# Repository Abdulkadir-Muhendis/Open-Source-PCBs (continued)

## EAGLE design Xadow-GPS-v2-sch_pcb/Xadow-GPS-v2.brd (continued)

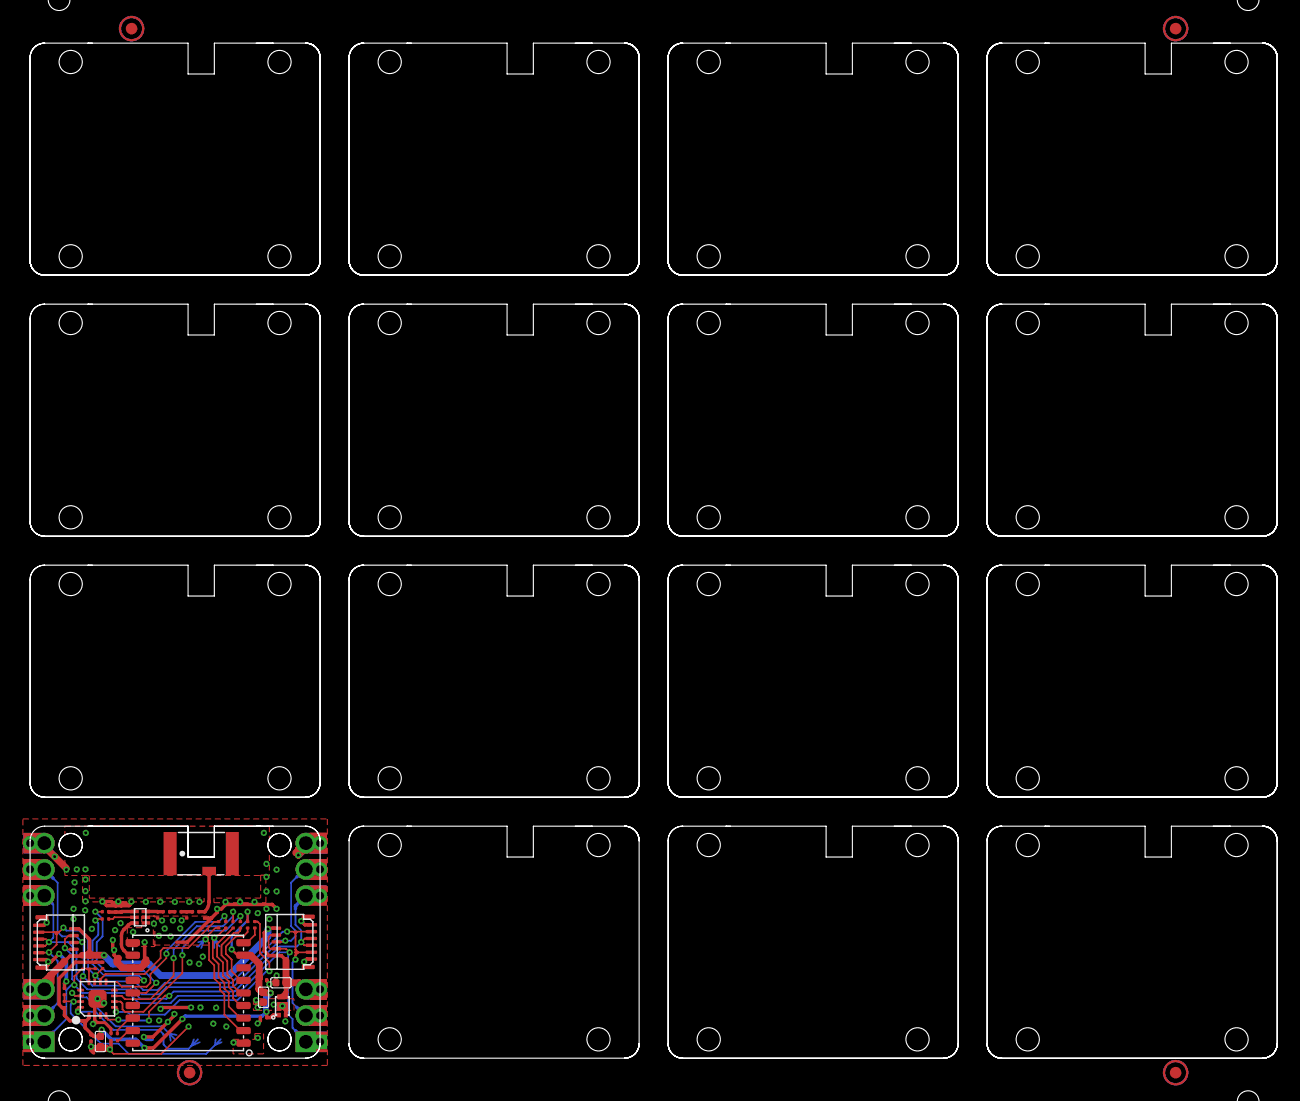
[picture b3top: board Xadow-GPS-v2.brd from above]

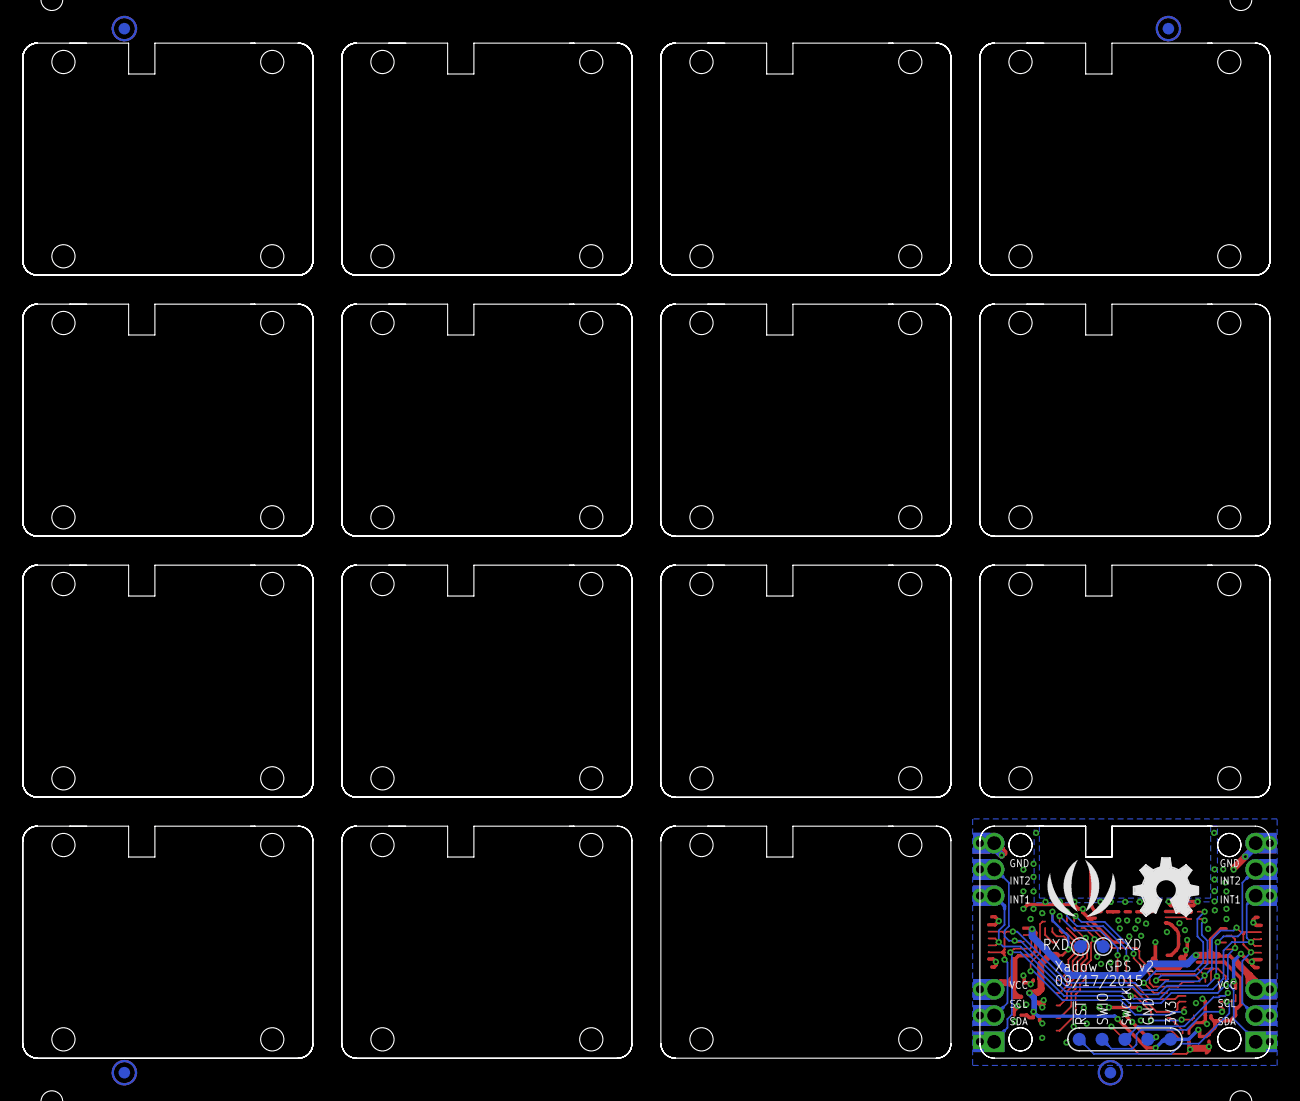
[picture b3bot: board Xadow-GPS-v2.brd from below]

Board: 2 copper layers, 109.2 x 88.9 mm, 53 parts (9 on the bottom side), 32 nets.

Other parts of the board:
U$19: OSHW_FILLX200_NOTEXT
U$21: SEEED-SILK-280*268MIL

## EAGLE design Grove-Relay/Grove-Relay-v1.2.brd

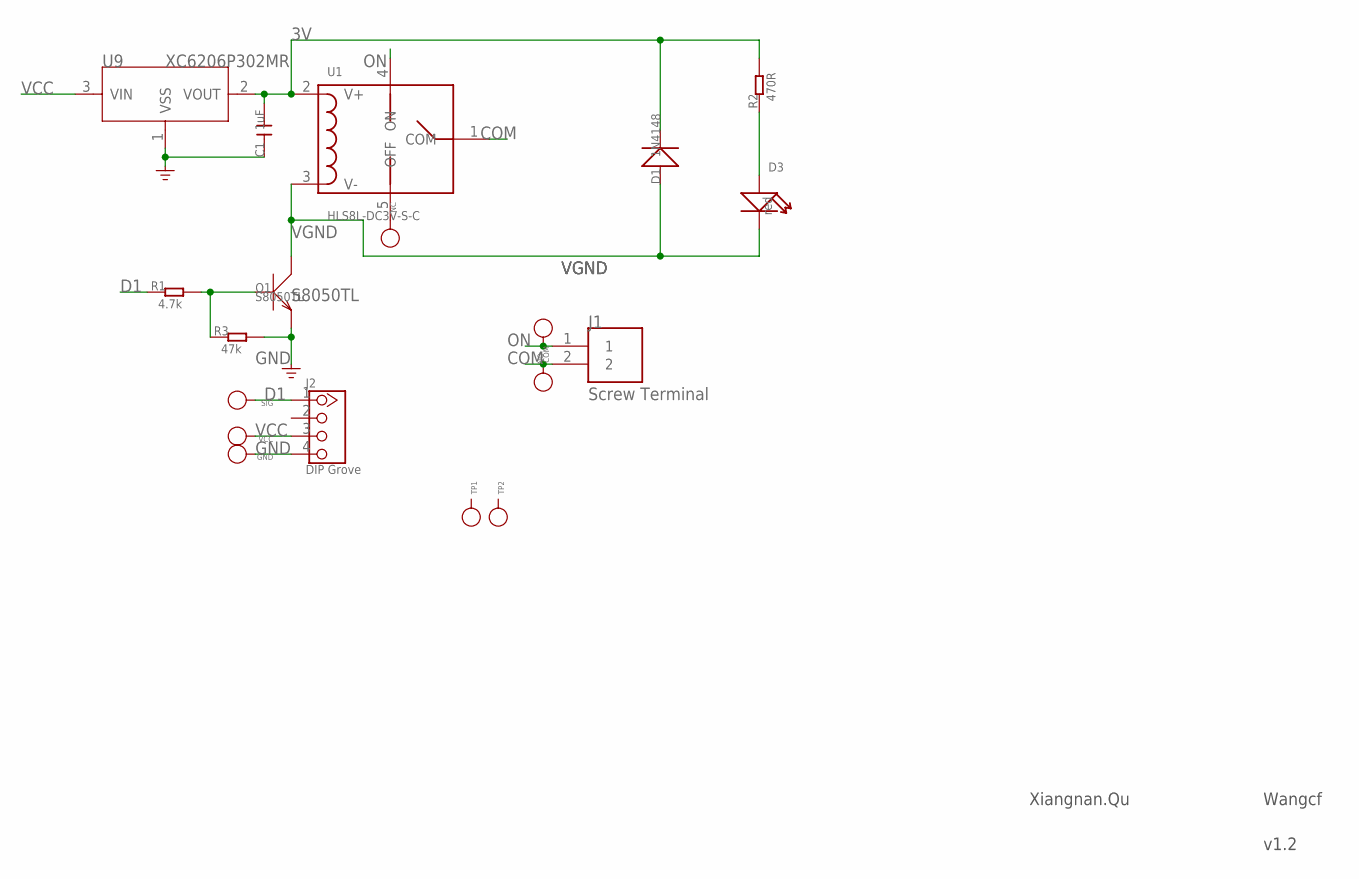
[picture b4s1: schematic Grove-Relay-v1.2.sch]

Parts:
C1: 1uF; C0603
COM: PAD-TEST-POINT'4545'; TP_4545
D1: 1N4148; LL-34
D3: red; LED-0603
GND: PAD-TEST-POINT'4545'; TP_4545
J1: Screw Terminal; CON2
J2: DIP Grove; 2.0_1X4
NC: PAD-TEST-POINT'4545'; TP_4545
NO: PAD-TEST-POINT'4545'; TP_4545
Q1: S8050TL; SOT23
R1: 4.7k; R0603
R2: 470R; R0603
R3: 47k; R0603
SIG: PAD-TEST-POINT'4545'; TP_4545
TP1, TP2: PAD-TEST-POINT'4545'; TP_4545
U1: HLS8L-DC3V-S-C; RELAY
U9: XC6206P302MR; SOT23
VCC: PAD-TEST-POINT'4545'; TP_4545

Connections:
3V: C1.2, D1.C (-), R2.2, U1.2 (V+), U9.2 (VOUT)
COM: COM.T, J1.2, U1.1 (COM)
D1: J2.1, R1.1, SIG.T
GND: C1.1, GND.T, J2.4, Q1.2 (E), R3.2, U9.1 (VSS)
unnamed: D3.+, R2.1
unnamed: Q1.1 (B), R1.2, R3.1
unnamed: NC.T, U1.5 (OFF)
ON: J1.1, NO.T, U1.4 (ON)
VCC: J2.3, U9.3 (VIN), VCC.T
VGND: D1.A (+), D3.-, Q1.3 (C), U1.3 (V-)

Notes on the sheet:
S8050TL
Xiangnan.Qu
Wangcf
v1.2

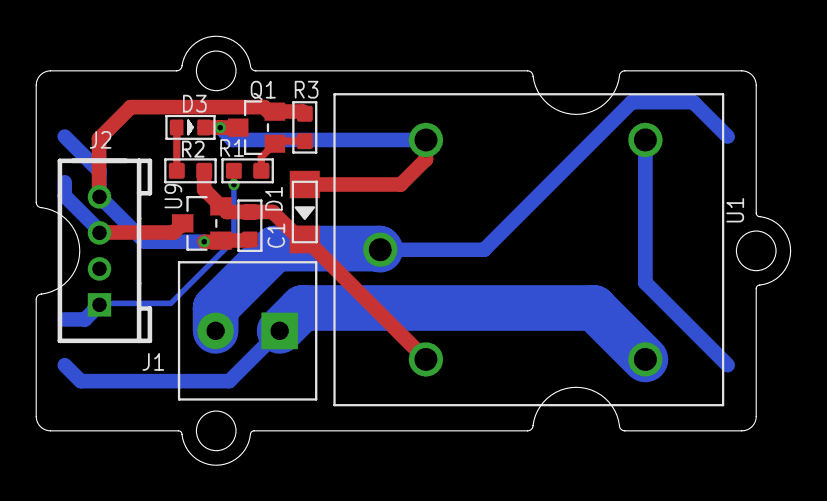
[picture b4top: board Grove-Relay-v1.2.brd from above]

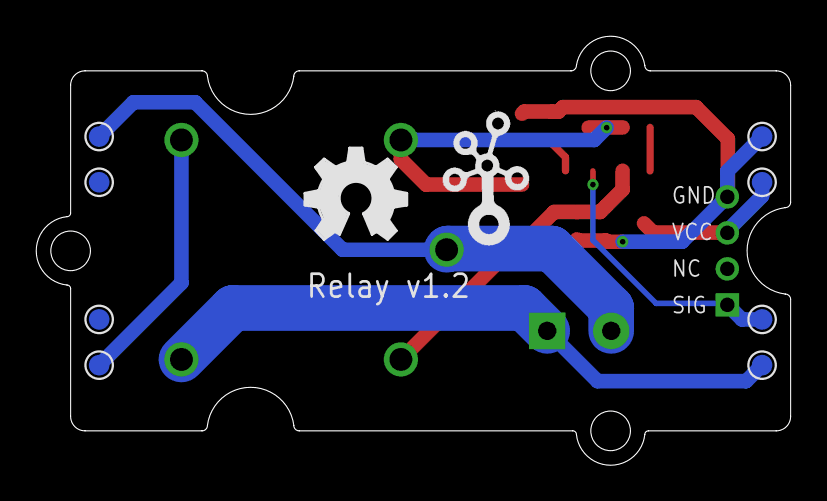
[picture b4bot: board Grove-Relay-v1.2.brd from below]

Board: 2 copper layers, 41.9 x 23.8 mm, 22 parts (10 on the bottom side), 10 nets.

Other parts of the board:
U$2: OSHW_FILLX200_NOTEXT
U$3: GROVE-TEST-PLATFORM
U$5: TWIGLOGO

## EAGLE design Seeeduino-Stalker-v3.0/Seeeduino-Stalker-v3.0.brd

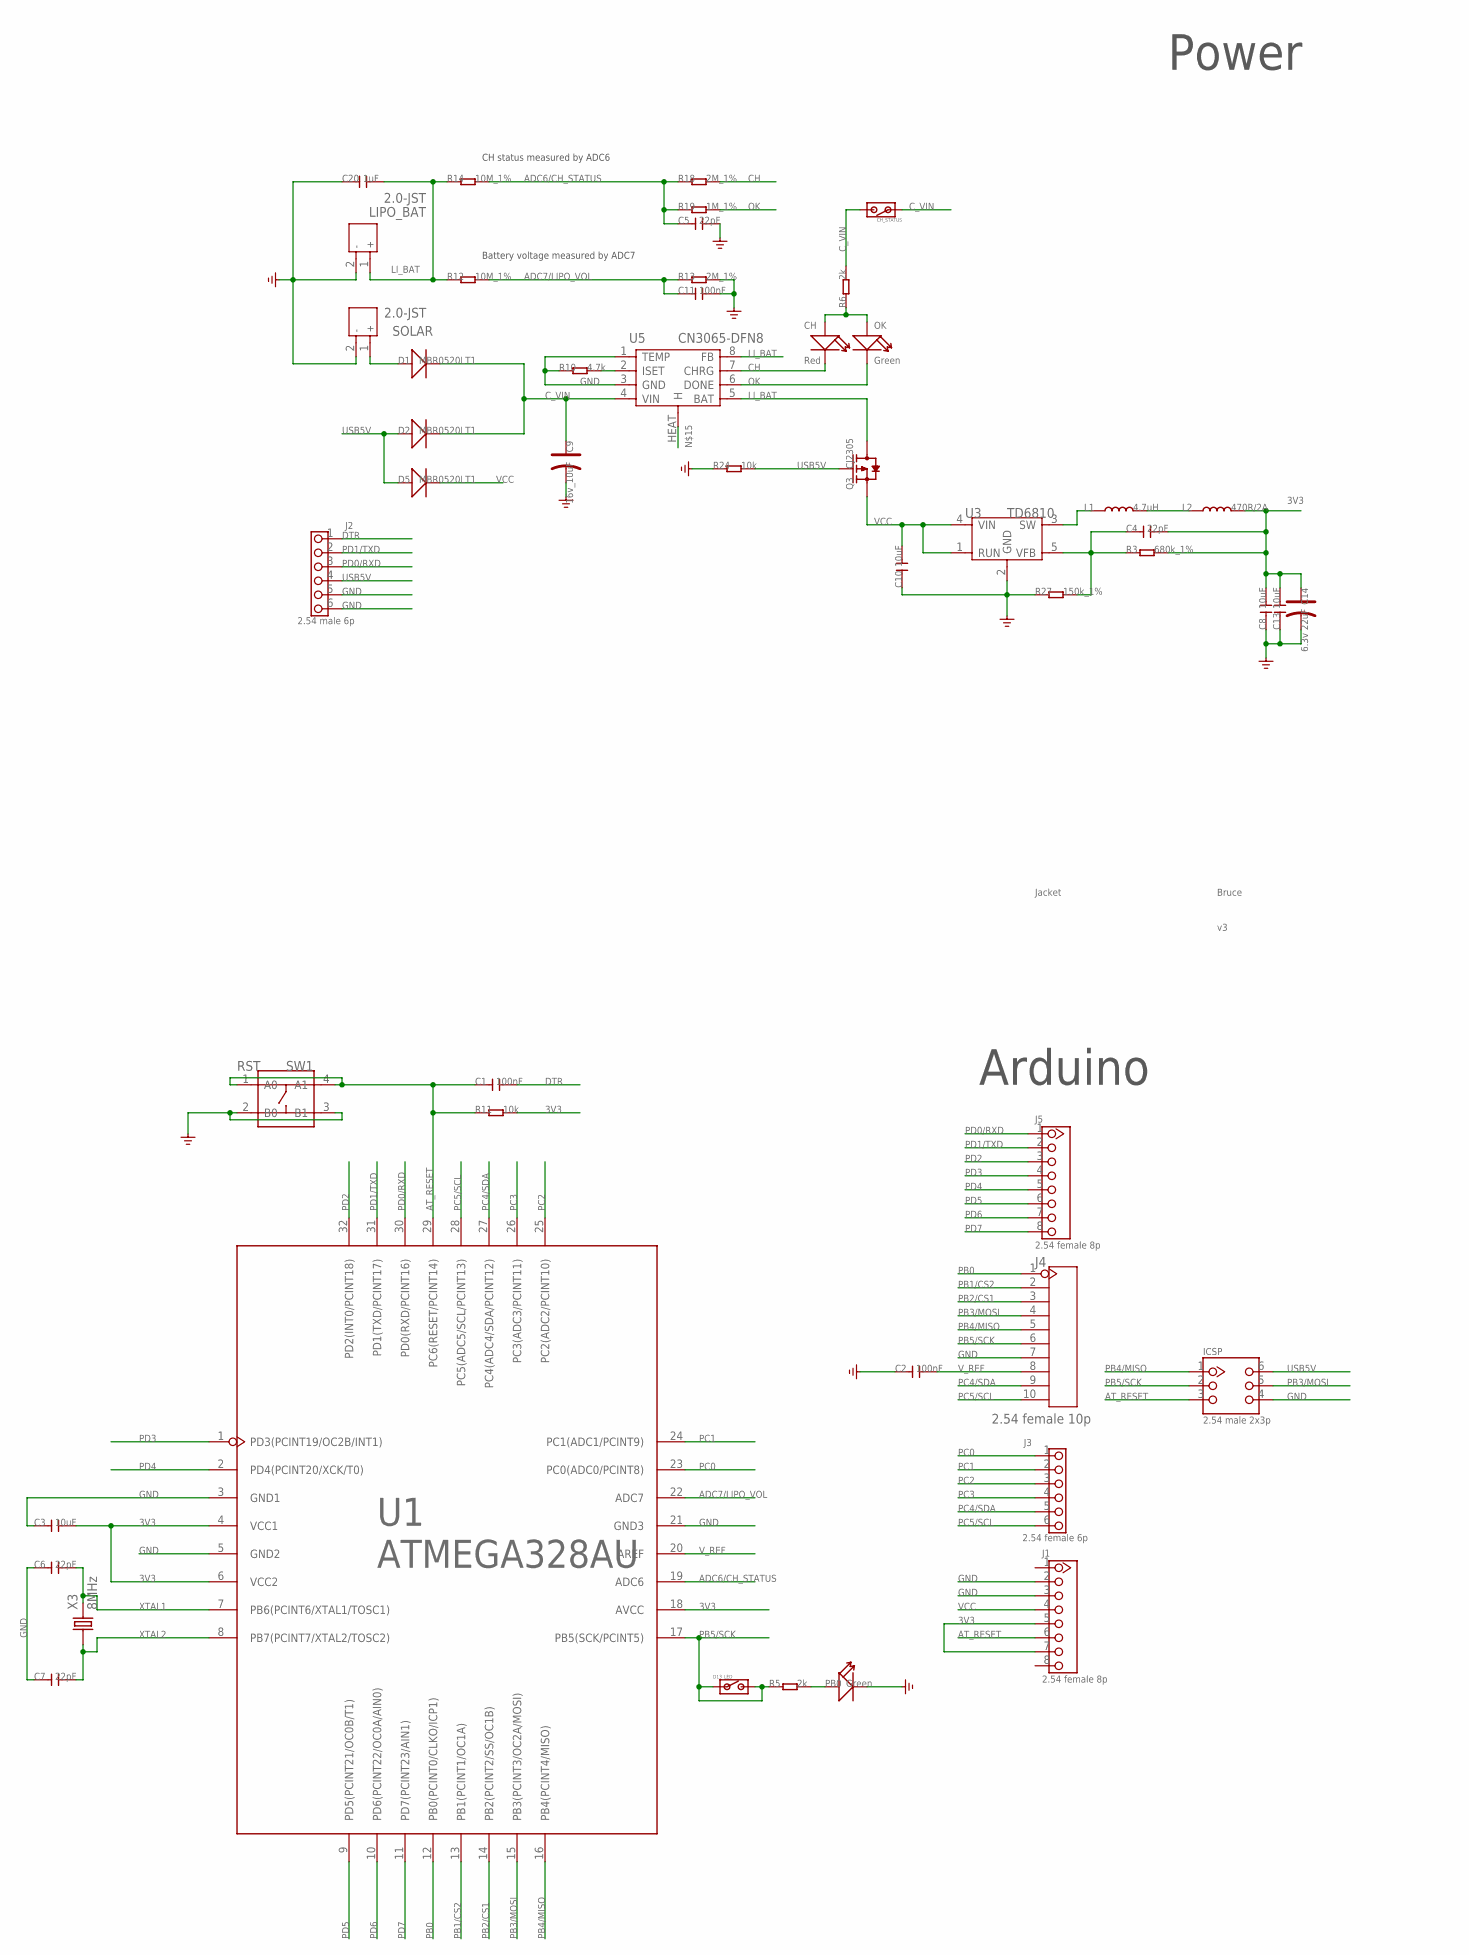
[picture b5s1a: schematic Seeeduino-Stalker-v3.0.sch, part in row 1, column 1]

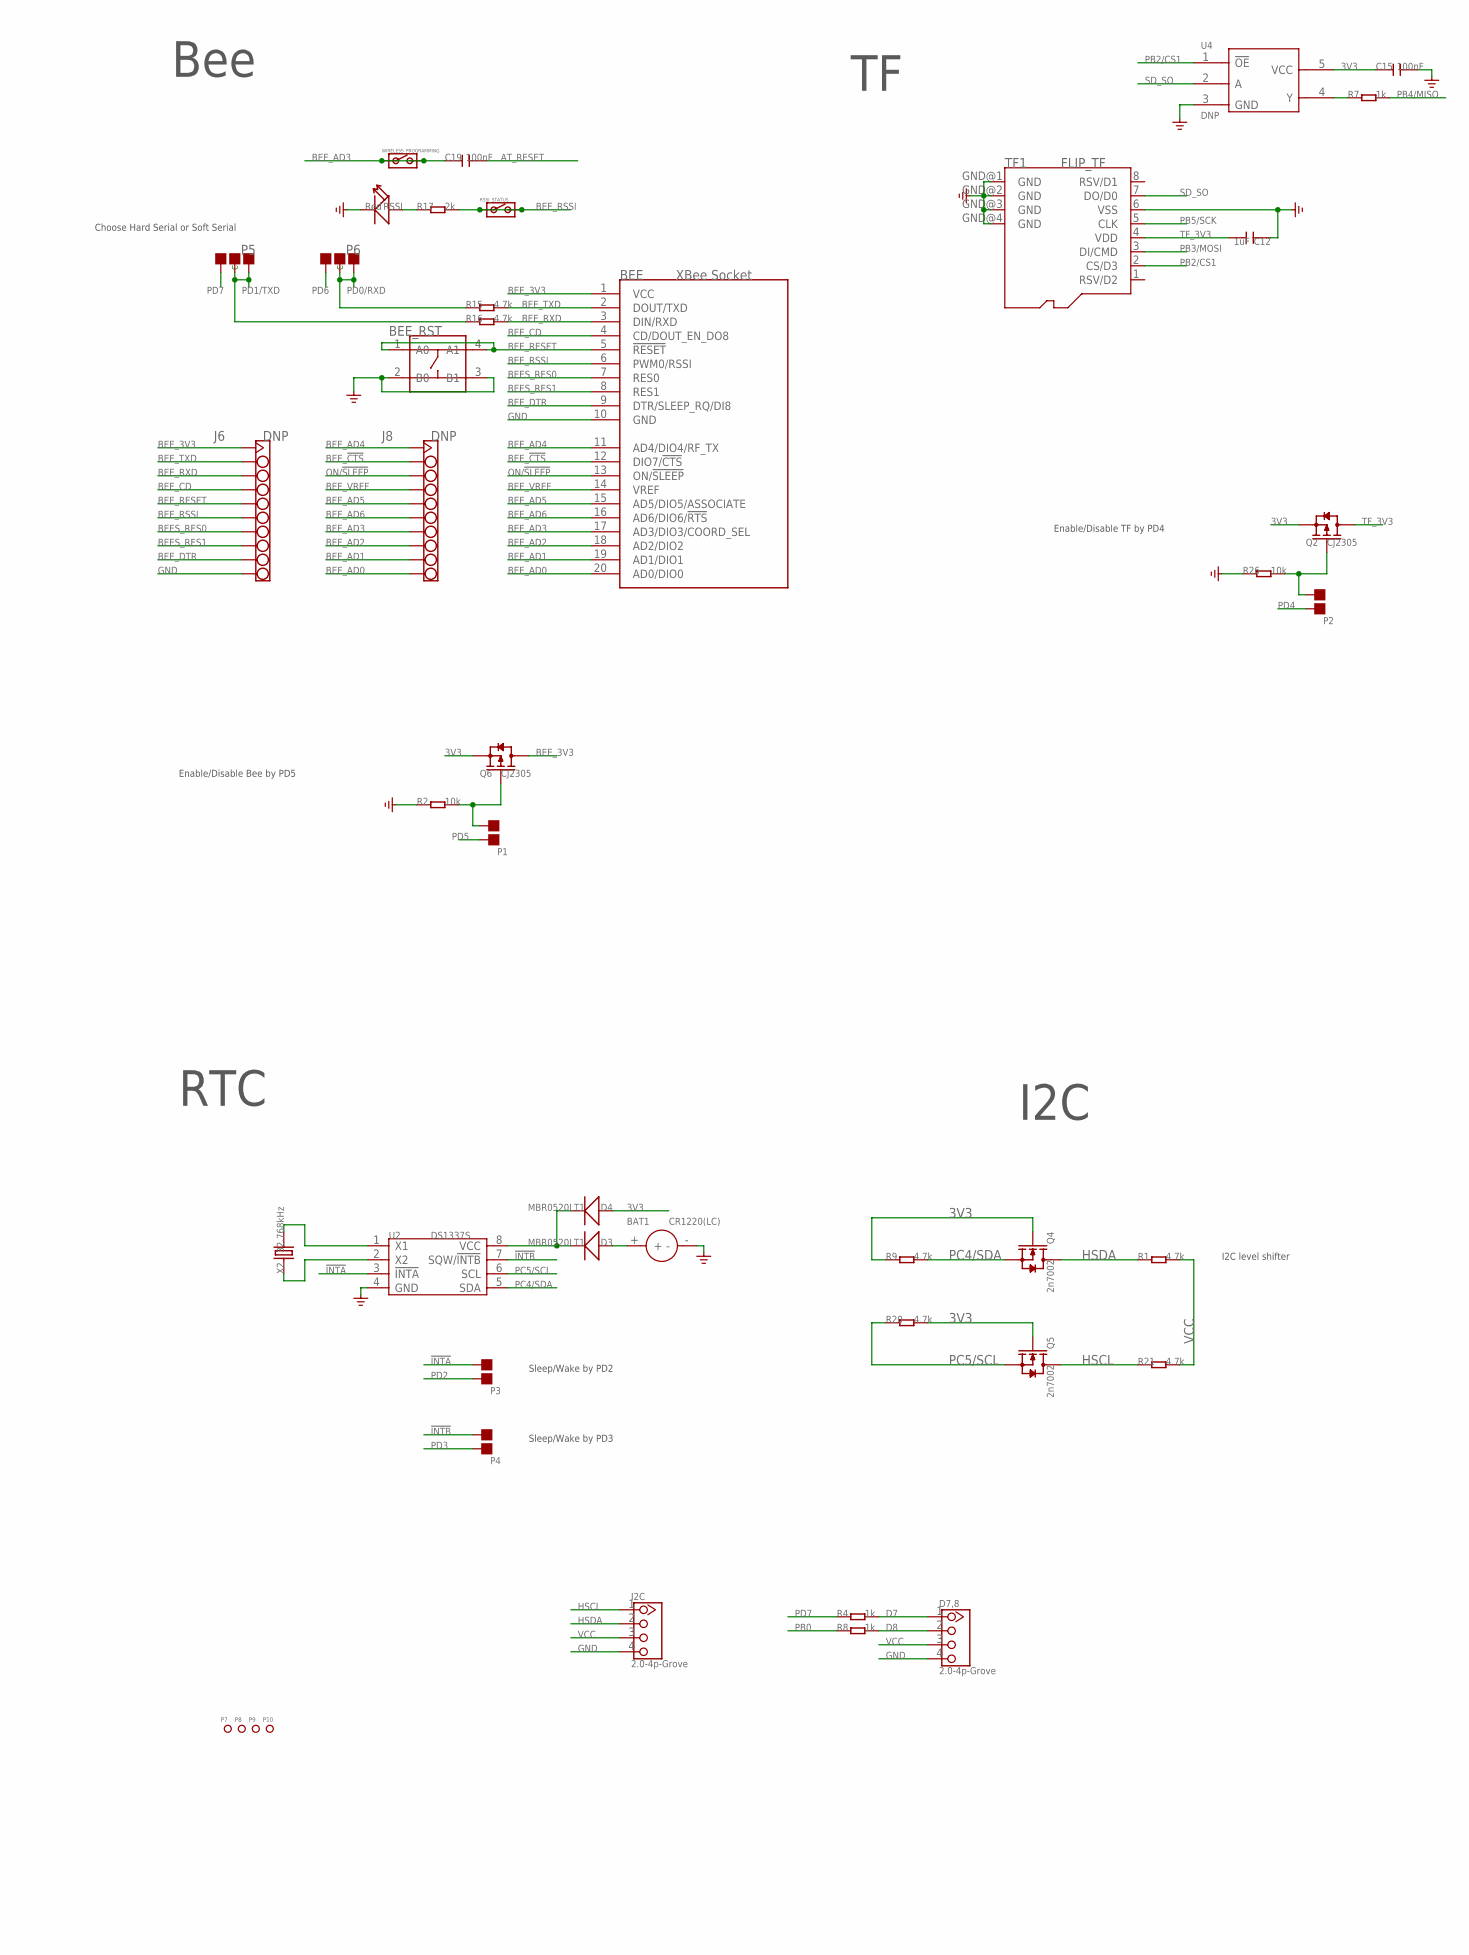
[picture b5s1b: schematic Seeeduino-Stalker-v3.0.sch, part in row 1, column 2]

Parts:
BAT1: CR1220(LC); 2P-D12.55X2.22H
BEE: XBee Socket; BEE
BEE_RST: SW2; 4P-SMD-6.2X6.2X4H
C1, C2, C11, C15, C19: 100nF; C0603
C3, C8, C10, C13: 10uF; C0805
C4, C5, C6, C7: 22pF; C0603
C9: 16v_10uF; AVX-A
C12, C20: 1uF; C0805
C14: 6.3v 22uF; AVX-A
CH: Red; D0603
CH_STATUS: DNP; JP_SW
D1, D2, D3, D4, D5: MBR0520LT1; SOD123-2.7X1.6
D7,8: 2.0-4p-Grove; 4P-2.0
D13_LED: DNP; JP_SW
I2C: 2.0-4p-Grove; 4P-2.0
ICSP: 2.54 male 2x3p; 2X3P-2.54-LEADED
J1, J5: 2.54 female 8p; 8P-2.54-LEADED
J2: 2.54 male 6p; 6P-2.54-LEADED
J3: 2.54 female 6p; 6P-2.54-LEADED
J4: 2.54 female 10p; 10P-2.54
J6, J8: DNP; HEADER_1X10
L1: 4.7uH; L0420
L2: 470R/2A; L0805
LIPO_BAT: 2.0-JST; JST-2.0
OK: Green; D0603
P1, P2, P3, P4: DNP; 2P-SMD-1.78X1.27
P5, P6: DNP; 3P-SMD-4.1X1.5
P7, P8, P9, P10: PAD-MARK; ROUND-MARK-1.0
PB0: Green; D0603
Q2, Q3, Q6: CJ2305; SOT23
Q4, Q5: 2n7002; SOT23
R1, R9, R10, R15, R16, R20, R21: 4.7k; 0603@1
R2, R11, R24, R26: 10k; 0603@1
R3: 680k_1%; 0603@1
R4, R7, R8: 1k; 0603@1
R5, R6, R17: 2k; 0603@1
R12, R14: 10M_1%; 0603@1
R13, R18: 2M_1%; 0603@1
R19: 1M_1%; 0603@1
R27: 150k_1%; 0603@1
RSSI: Red; D0603
RSSI_STATUS: DNP; JP_SW
RST: SW1; 4P-SMD-6.2X6.2X4H
SOLAR: 2.0-JST; JST-2.0
TF1: FLIP_TF
U1: ATMEGA328AU; ATMEGA168-20AU
U2: DS1337S; SOP8
U3: TD6810; SOT23-5
U4: DNP; SOT353
U5: CN3065-DFN8; DFN8
WIRELESS_PROGRAMMING: DNP; JP_SW
X2: 32.768kHz; 2P-SMD-3.2X1.5
X3: 8MHz; HC49/S

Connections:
3V3: C3.2, C4.2, C8.2, C13.2, C14.+, C15.1, D4.1 (+), J1.5, J1.7, L2.2, Q2.2 (S), Q4.1 (G), Q5.1 (G), Q6.2 (S), R3.2, R9.1, R11.2, R20.2, U1.4 (VCC1), U1.6 (VCC2), U1.18 (AVCC), U4.5 (VCC)
!INTA: P3.1, U2.3 (!INTA)
!INTB: P4.1, U2.7 (SQW/!INTB)
ADC6/CH_STATUS: C5.1, R14.2, R18.1, R19.1, U1.19 (ADC6)
ADC7/LIPO_VOL: C11.1, R12.2, R13.1, U1.22 (ADC7)
AT_RESET: C1.1, C19.2, ICSP.3, J1.6, R11.1, RST.1 (A0), RST.4 (A1), U1.29 (PC6(RESET/PCINT14))
BEES_RES0: BEE.7 (RES0), J6.7
BEES_RES1: BEE.8 (RES1), J6.8
BEE_3V3: BEE.1 (VCC), J6.1, Q6.3 (D)
BEE_!CTS: BEE.12 (DIO7/!CTS), J8.2
BEE_AD0: BEE.20 (AD0/DIO0), J8.10
BEE_AD1: BEE.19 (AD1/DIO1), J8.9
BEE_AD2: BEE.18 (AD2/DIO2), J8.8
BEE_AD3: BEE.17 (AD3/DIO3/COORD_SEL), C19.1, J8.7, WIRELESS_PROGRAMMING.1, WIRELESS_PROGRAMMING.2
BEE_AD4: BEE.11 (AD4/DIO4/RF_TX), J8.1
BEE_AD5: BEE.15 (AD5/DIO5/ASSOCIATE), J8.5
BEE_AD6: BEE.16 (AD6/DIO6/!RTS), J8.6
BEE_CD: BEE.4 (CD/DOUT_EN_DO8), J6.4
BEE_DTR: BEE.9 (DTR/SLEEP_RQ/DI8), J6.9
BEE_RESET: BEE.5 (!RESET), BEE_RST.1 (A0), BEE_RST.4 (A1), J6.5
BEE_RSSI: BEE.6 (PWM0/RSSI), J6.6, R17.2, RSSI_STATUS.1, RSSI_STATUS.2
BEE_RXD: BEE.3 (DIN/RXD), J6.3, R16.2
BEE_TXD: BEE.2 (DOUT/TXD), J6.2, R15.2
BEE_VREF: BEE.14 (VREF), J8.4
CH: CH.-, R18.2, U5.7 (CHRG)
C_VIN: C9.+, CH_STATUS.1, CH_STATUS.2, D1.2 (-), D2.2 (-), R6.2, U5.4 (VIN)
D7: D7,8.1, R4.2
D8: D7,8.2, R8.2
DTR: C1.2, J2.1
GND: BAT1.-, BEE.10 (GND), BEE_RST.2 (B0), BEE_RST.3 (B1), C2.1, C3.1, C5.2, C6.1, C7.1, C8.1, C9.-, C10.1, C11.2, C12.1, C13.1, C14.-, C15.2, C20.1, D7,8.4, I2C.4, ICSP.4, J1.2, J1.3, J2.5, J2.6, J4.7, J6.10, LIPO_BAT.2, PB0.-, R2.1, R10.1, R13.2, R24.1, R26.1, R27.1, RSSI.-, RST.2 (B0), RST.3 (B1), SOLAR.2, TF1.6 (VSS), TF1.GND@1 (GND), TF1.GND@2 (GND), TF1.GND@3 (GND), TF1.GND@4 (GND), U1.3 (GND1), U1.5 (GND2), U1.21 (GND3), U2.4 (GND), U3.2 (GND), U4.3 (GND), U5.1 (TEMP), U5.3 (GND)
HSCL: I2C.1, Q5.3 (D), R21.1
HSDA: I2C.2, Q4.3 (D), R1.1
LI_BAT: C20.2, LIPO_BAT.1, Q3.3 (D), R12.1, R14.1, U5.5 (BAT), U5.8 (FB)
unnamed: PB0.+, R5.2
unnamed: D3.2 (-), D4.2 (-), U2.8 (VCC)
unnamed: D1.1 (+), SOLAR.1
unnamed: BAT1.+, D3.1 (+)
unnamed: R10.2, U5.2 (ISET)
unnamed: R17.1, RSSI.+
unnamed: U2.1 (X1), X2.2
unnamed: CH.+, OK.+, R6.1
unnamed: U2.2 (X2), X2.1
unnamed: C4.1, R3.1, R27.2, U3.5 (VFB)
unnamed: P1.1, Q6.1 (G), R2.2
unnamed: P2.1, Q2.1 (G), R26.2
unnamed: L1.2, L2.1
unnamed: L1.1, U3.3 (SW)
unnamed: R7.1, U4.4 (Y)
OK: OK.-, R19.2, U5.6 (DONE)
ON/!SLEEP: BEE.13 (ON/!SLEEP), J8.3
PB0: J4.1, R8.1, U1.12 (PB0(PCINT0/CLKO/ICP1))
PB1/CS2: J4.2, U1.13 (PB1(PCINT1/OC1A))
PB2/CS1: J4.3, TF1.2 (CS/D3), U1.14 (PB2(PCINT2/SS/OC1B)), U4.1 (!OE!)
PB3/MOSI: ICSP.5, J4.4, TF1.3 (DI/CMD), U1.15 (PB3(PCINT3/OC2A/MOSI))
PB4/MISO: ICSP.1, J4.5, R7.2, U1.16 (PB4(PCINT4/MISO))
PB5/SCK: D13_LED.1, D13_LED.2, ICSP.2, J4.6, R5.1, TF1.5 (CLK), U1.17 (PB5(SCK/PCINT5))
PC0: J3.1, U1.23 (PC0(ADC0/PCINT8))
PC1: J3.2, U1.24 (PC1(ADC1/PCINT9))
PC2: J3.3, U1.25 (PC2(ADC2/PCINT10))
PC3: J3.4, U1.26 (PC3(ADC3/PCINT11))
PC4/SDA: J3.5, J4.9, Q4.2 (S), R9.2, U1.27 (PC4(ADC4/SDA/PCINT12)), U2.5 (SDA)
PC5/SCL: J3.6, J4.10, Q5.2 (S), R20.1, U1.28 (PC5(ADC5/SCL/PCINT13)), U2.6 (SCL)
PD0/RXD: J2.3, J5.1, P6.11 (R), P6.MM (C), R15.1, U1.30 (PD0(RXD/PCINT16))
PD1/TXD: J2.2, J5.2, P5.11 (R), P5.MM (C), R16.1, U1.31 (PD1(TXD/PCINT17))
PD2: J5.3, P3.2, U1.32 (PD2(INT0/PCINT18))
PD3: J5.4, P4.2, U1.1 (PD3(PCINT19/OC2B/INT1))
PD4: J5.5, P2.2, U1.2 (PD4(PCINT20/XCK/T0))
PD5: J5.6, P1.2, U1.9 (PD5(PCINT21/OC0B/T1))
PD6: J5.7, P6.00 (L), U1.10 (PD6(PCINT22/OC0A/AIN0))
PD7: J5.8, P5.00 (L), R4.1, U1.11 (PD7(PCINT23/AIN1))
SD_SO: TF1.7 (DO/D0), U4.2 (A)
TF_3V3: C12.2, Q2.3 (D), TF1.4 (VDD)
USB5V: D2.1 (+), D5.1 (+), ICSP.6, J2.4, Q3.1 (G), R24.2
VCC: C10.2, D5.2 (-), D7,8.3, I2C.3, J1.4, Q3.2 (S), R1.2, R21.2, U3.1 (RUN), U3.4 (VIN)
V_REF: C2.2, J4.8, U1.20 (AREF)
XTAL1: C6.2, U1.7 (PB6(PCINT6/XTAL1/TOSC1)), X3.2
XTAL2: C7.2, U1.8 (PB7(PCINT7/XTAL2/TOSC2)), X3.1

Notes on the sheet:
Power
Arduino
Bee
Battery voltage measured by ADC7
RTC
I2C
I2C level shifter
Sleep/Wake by PD2
Sleep/Wake by PD3
Enable/Disable Bee by PD5
CH status measured by ADC6
Enable/Disable TF by PD4
Choose Hard Serial or Soft Serial
Jacket
Bruce

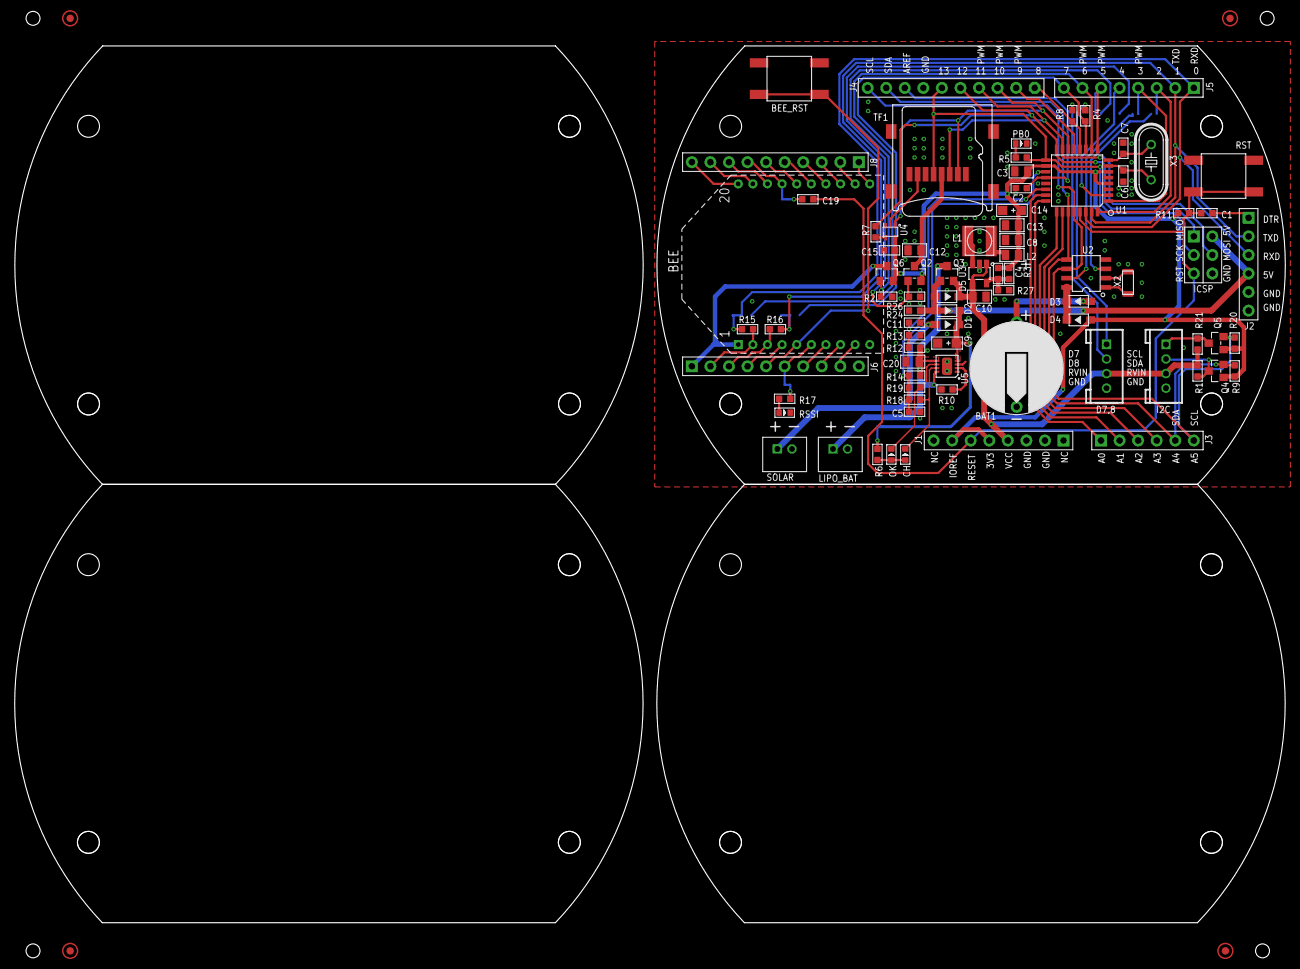
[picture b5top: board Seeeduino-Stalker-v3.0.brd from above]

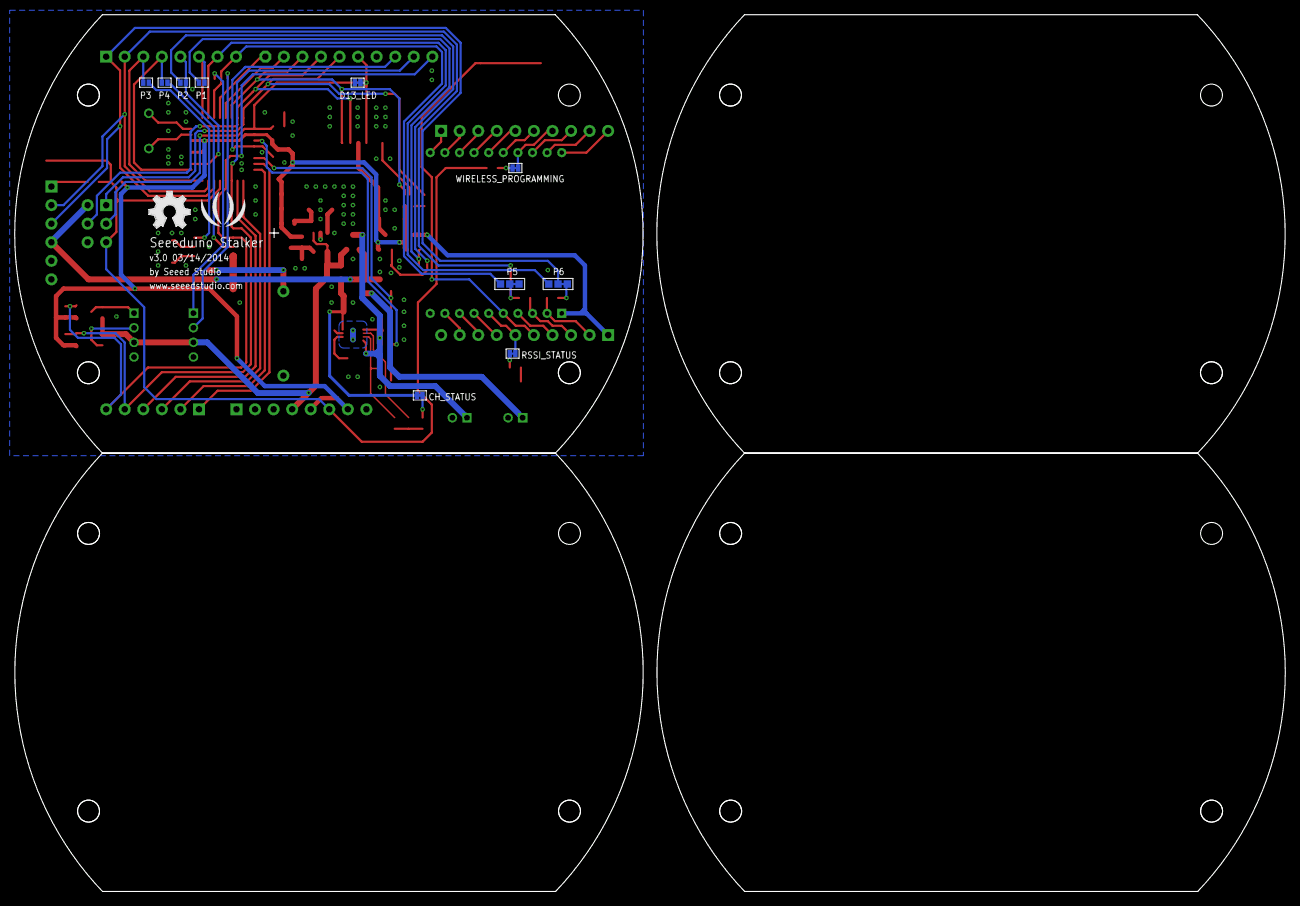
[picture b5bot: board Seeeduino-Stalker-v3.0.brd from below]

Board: 2 copper layers, 173.9 x 120.0 mm, 97 parts (12 on the bottom side), 77 nets.

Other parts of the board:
U$23: OSHW_FILLX200_NOTEXT
U$24: LOGO_SILK

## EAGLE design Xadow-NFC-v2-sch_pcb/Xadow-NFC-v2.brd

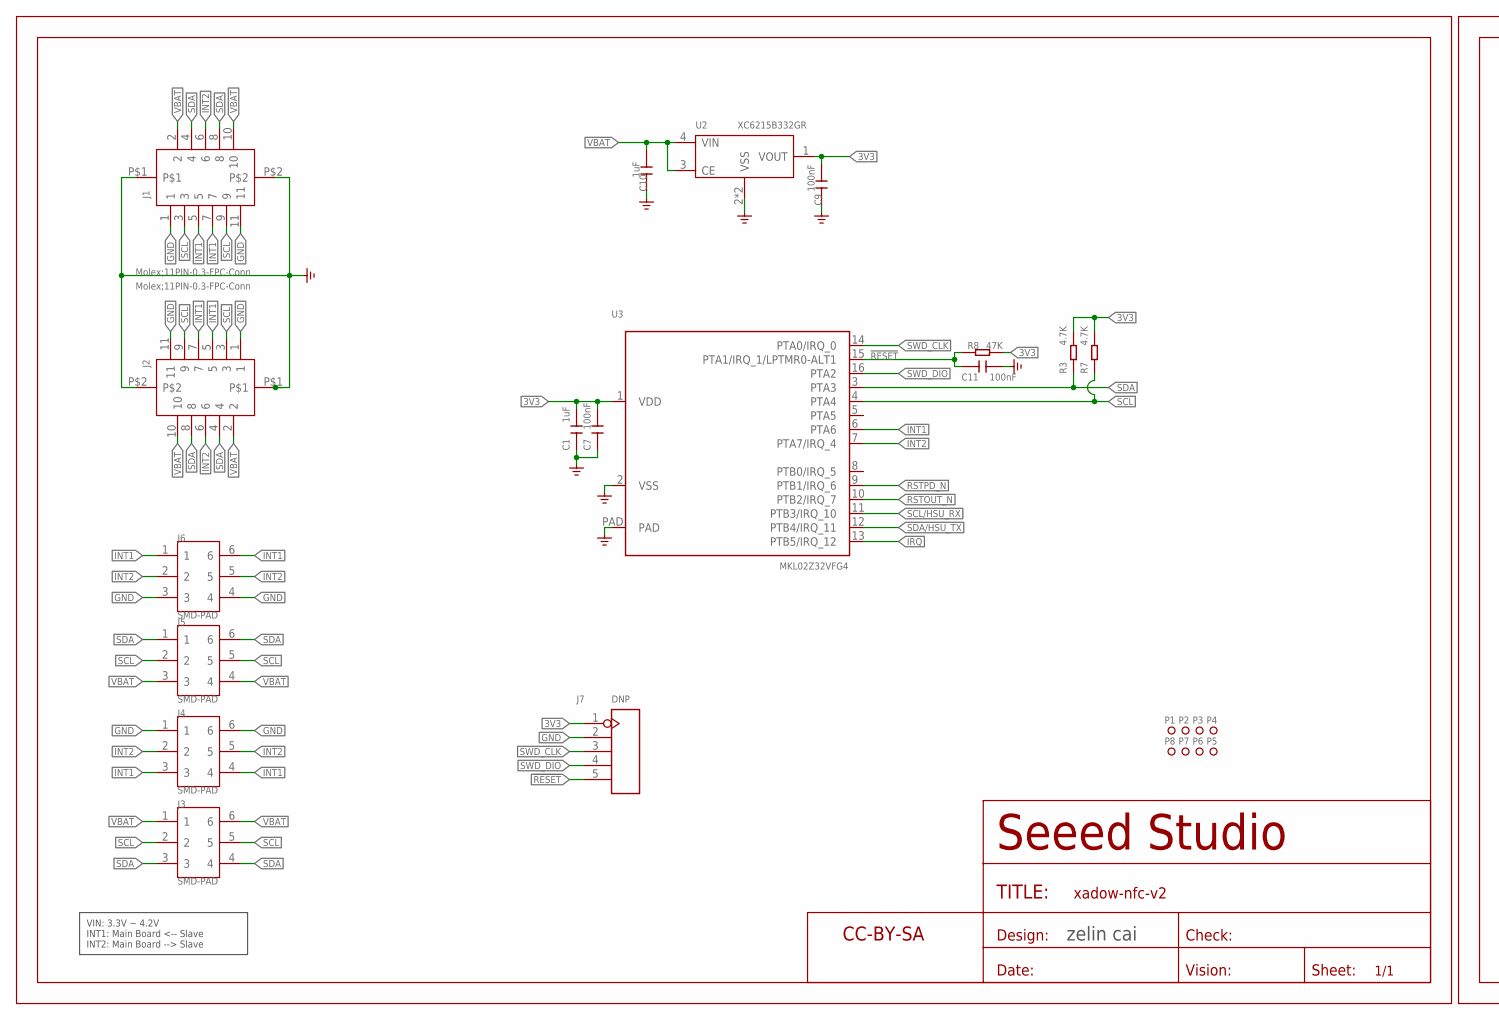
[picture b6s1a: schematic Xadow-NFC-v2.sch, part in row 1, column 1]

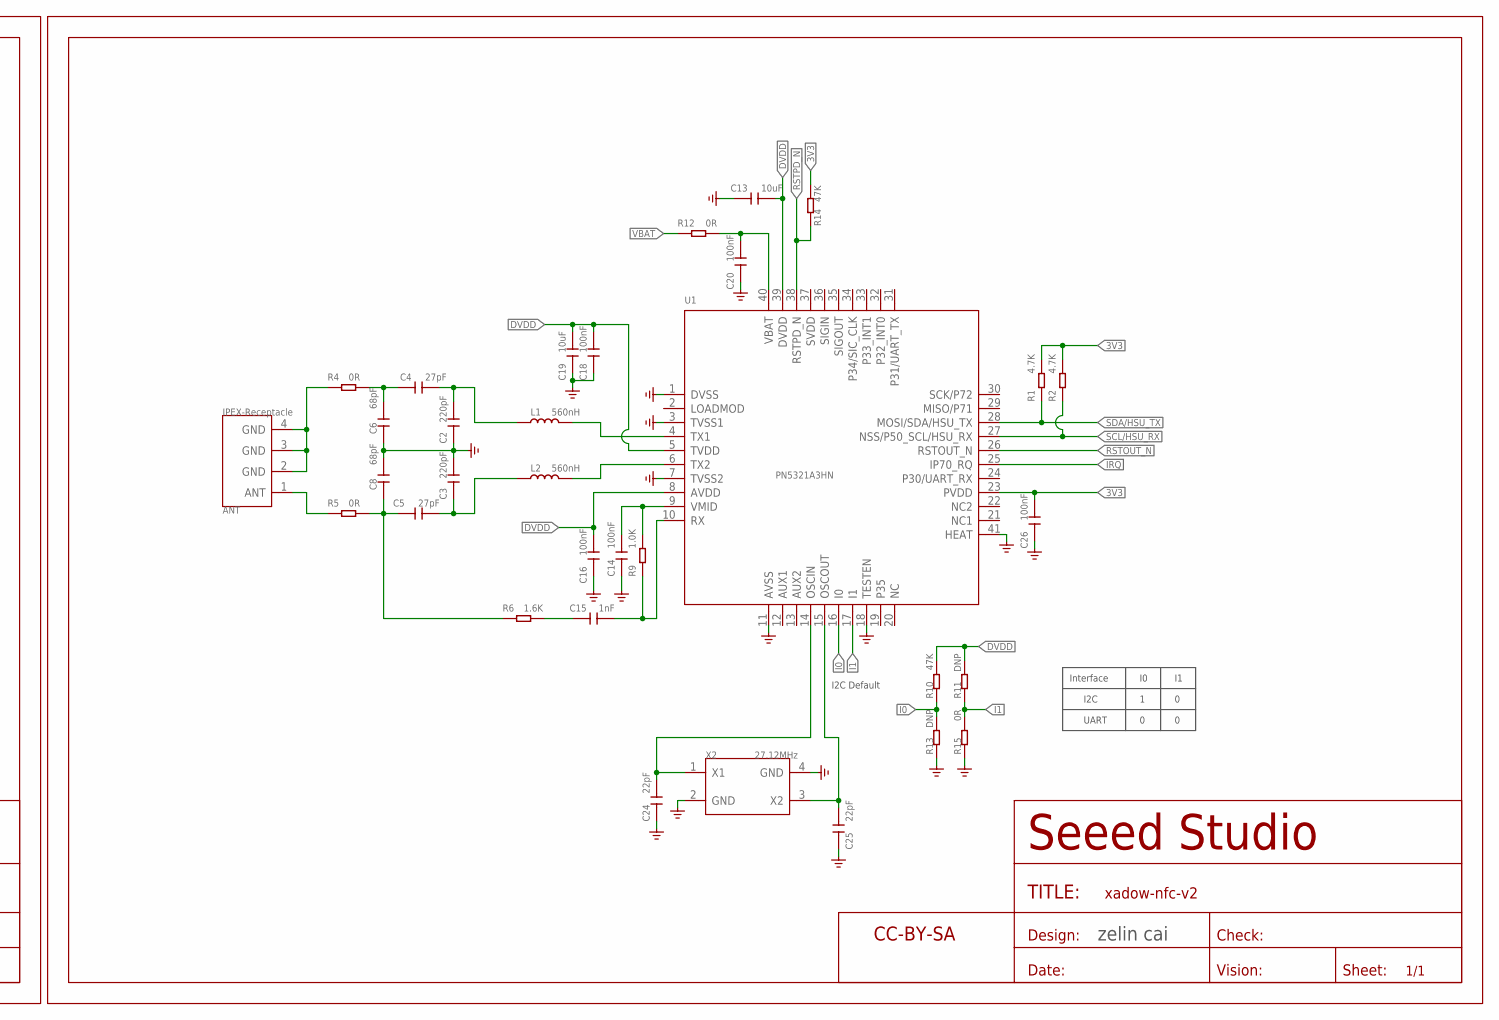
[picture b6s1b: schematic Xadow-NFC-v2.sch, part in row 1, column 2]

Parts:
ANT: IPEX-Receptacle; ANT-IPEX4-1.7X1.7MM
C1, C10: 1uF; C0402
C2, C3: 220pF; C0402
C4, C5: 27pF; C0402
C6, C8: 68pF; C0402
C7, C9, C11, C14, C16, C18, C20, C26: 100nF; C0402
C13, C19: 10uF; C0402
C15: 1nF; C0402
C24, C25: 22pF; C0402
J1, J2: Molex;11PIN-0.3-FPC-Conn; FPC11-SMD-0.3(FH35C)
J3: SMD-PAD; 6P-DIP-2_S3
J4, J6: SMD-PAD; 6P-DIP-2_ROUND
J5: SMD-PAD; 6P-DIP-2
J7: DNP; H5-SMD-2.0-TEST
L1, L2: 560nH; L0603
P1, P2, P3, P4, P5, P6, P7, P8: MRK; ROUND-MARK-1.0
R1, R2, R3, R7: 4.7K; R0402
R4, R5, R12, R15: 0R; R0402
R6: 1.6K; R0402
R8, R10, R14: 47K; R0402
R9: 1.0K; R0402
R11, R13: DNP; R0402
U1: PN5321A3HN; QFN40G-0.5-6X6MM
U2: XC6215B332GR; USP4-0.6-1.2X1.6MM
U3: MKL02Z32VFG4; QFN16G-0.5-3X3MM
U$1: PAGE1; SEEEDSTUDIO-PCB-FRAME
U$21: PAGE2; SEEEDSTUDIO-PCB-FRAME
X2: 27.12MHz; SMD4P-2.0X1.6X0.5MM

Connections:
3V3: C1.2, C7.2, C9.2, C26.2, J7.1, R1.2, R2.2, R3.2, R7.2, R8.2, R14.2, U1.23 (PVDD), U2.1 (VOUT), U3.1 (VDD)
!RESET: C11.1, J7.5, R8.1, U3.15 (PTA1/IRQ_1/LPTMR0-ALT1)
DVDD: C13.1, C16.2, C18.2, C19.2, R10.1, R11.1, U1.5 (TVDD), U1.8 (AVDD), U1.39 (DVDD)
GND: C1.1, C2.1, C3.2, C6.2, C7.1, C8.1, C9.1, C10.1, C11.2, C13.2, C14.1, C16.1, C18.1, C19.1, C20.1, C24.1, C25.1, C26.1, J1.1, J1.11, J1.P$1, J1.P$2, J2.1, J2.11, J2.P$1, J2.P$2, J4.1, J4.6, J6.3, J6.4, J7.2, R13.2, R15.2, U1.1 (DVSS), U1.3 (TVSS1), U1.7 (TVSS2), U1.11 (AVSS), U1.18 (TESTEN), U1.41 (HEAT), U2.2 (VSS), U2.PAD (VSS), U3.2 (VSS), U3.PAD, X2.2 (GND), X2.4 (GND)
I0: R10.2, R13.1, U1.16 (I0)
I1: R11.2, R15.1, U1.17 (I1)
INT1: J1.5, J1.7, J2.5, J2.7, J4.3, J4.4, J6.1, J6.6, U3.6 (PTA6)
INT2: J1.6, J2.6, J4.2, J4.5, J6.2, J6.5, U3.7 (PTA7/IRQ_4)
IRQ: U1.25 (IP70_RQ), U3.13 (PTB5/IRQ_12)
unnamed: C15.1, R9.1, U1.10 (RX)
unnamed: C14.2, R9.2, U1.9 (VMID)
unnamed: C3.1, C5.1, L2.1
unnamed: C2.2, C4.1, L1.1
unnamed: C4.2, C6.1, R4.2
unnamed: C5.2, C8.2, R5.2, R6.1
unnamed: ANT.2 (GND), ANT.3 (GND), ANT.4 (GND), R4.1
unnamed: ANT.1 (ANT), R5.1
unnamed: C15.2, R6.2
unnamed: C24.2, U1.14 (OSCIN), X2.1 (X1)
unnamed: C25.2, U1.15 (OSCOUT), X2.3 (X2)
RSTOUT_N: U1.26 (RSTOUT_N), U3.10 (PTB2/IRQ_7)
RSTPD_N: R14.1, U1.38 (RSTPD_N), U3.9 (PTB1/IRQ_6)
SCL: J1.3, J1.9, J2.3, J2.9, J3.2, J3.5, J5.2, J5.5, R7.1, U3.4 (PTA4)
SCL/HSU_RX: R2.1, U1.27 (NSS/P50_SCL/HSU_RX), U3.11 (PTB3/IRQ_10)
SDA: J1.4, J1.8, J2.4, J2.8, J3.3, J3.4, J5.1, J5.6, R3.1, U3.3 (PTA3)
SDA/HSU_TX: R1.1, U1.28 (MOSI/SDA/HSU_TX), U3.12 (PTB4/IRQ_11)
SWD_CLK: J7.3, U3.14 (PTA0/IRQ_0)
SWD_DIO: J7.4, U3.16 (PTA2)
TX_N: L1.2, U1.4 (TX1)
TX_P: L2.2, U1.6 (TX2)
VBAT: C10.2, C20.2, J1.2, J1.10, J2.2, J2.10, J3.1, J3.6, J5.3, J5.4, R12.1, R12.2, U1.40 (VBAT), U2.3 (CE), U2.4 (VIN)

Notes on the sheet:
zelin cai
VIN: 3.3V ~ 4.2V INT1: Main Board <-- Slave INT2: Main Board --> Slave
Interface
I2C
UART
I2C Default
